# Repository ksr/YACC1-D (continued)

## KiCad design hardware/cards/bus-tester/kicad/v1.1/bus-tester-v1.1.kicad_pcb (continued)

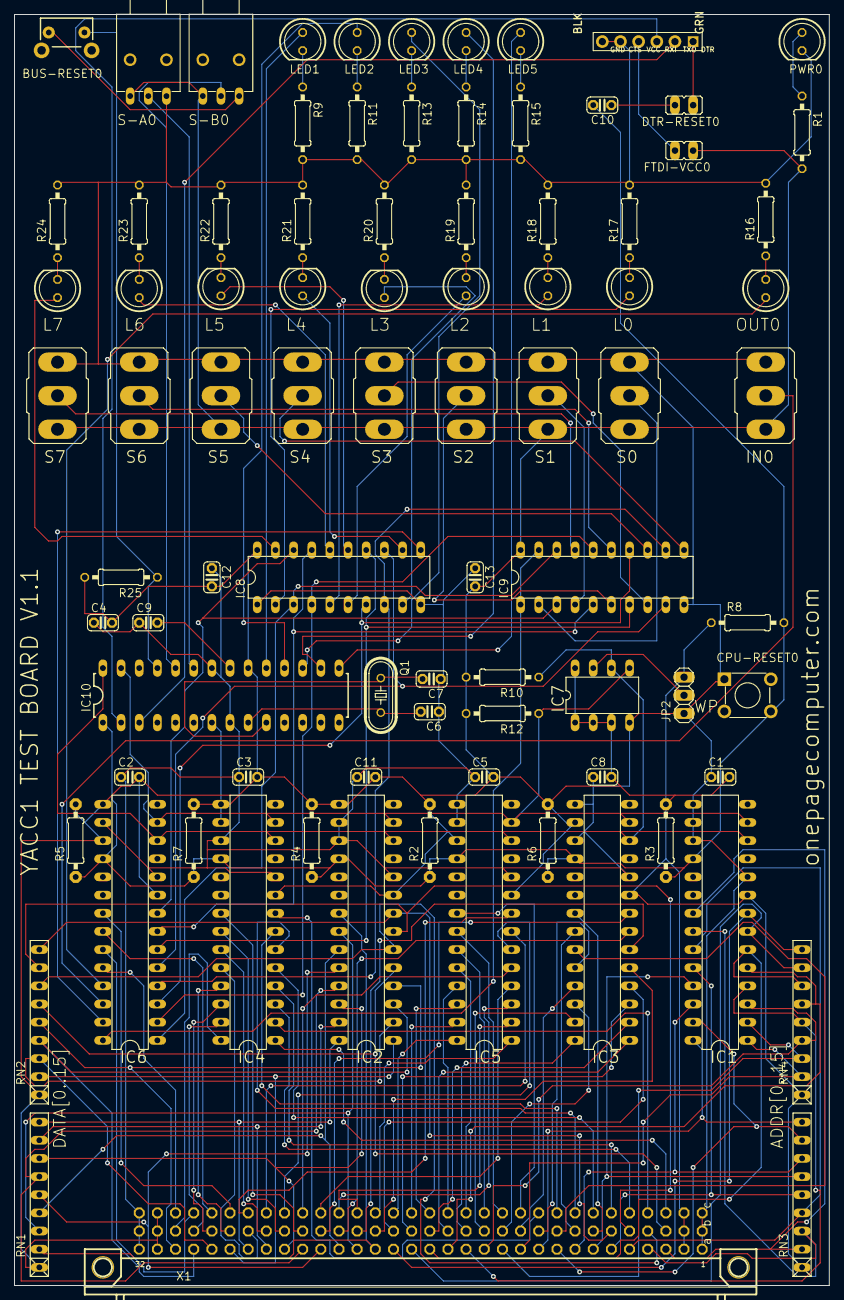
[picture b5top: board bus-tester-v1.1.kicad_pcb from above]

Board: 2 copper layers, 114.0 x 177.8 mm, 86 parts (0 on the bottom side), 149 nets.

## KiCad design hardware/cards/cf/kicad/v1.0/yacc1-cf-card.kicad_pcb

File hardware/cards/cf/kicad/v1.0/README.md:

# yacc1-cf-card v1.0 — KiCad design (generated from `cf_netlist.py`)

> **Not built (never ordered).** This design is the basis for the CF section planned on the memory card (decided
> 2026-09-24: same circuit, I/O-mapped on P8/P9, as the ROM and both emulators use; not designed yet). Theory:
> [`docs/cards/cf.md`](../../../../../docs/cards/cf.md).

The YACC1 CompactFlash card: a CF card in a commercial CF-to-IDE adapter, driven in 8-bit True IDE mode through two
I/O ports. P8 (write) is a 74LS175 latch holding the ATA register number (DA0-2) and a CF-reset bit; P9 (read/write)
is the selected ATA register through a 74LS245. A 74LS138 decodes the port and a 74LS32 gates the bus strobes. Theory of
operation: [`docs/cards/cf.md`](../../../../../docs/cards/cf.md).

**The circuit lives in `cf_netlist.py`** (parts, nets, no-connects, `check()`). `gen_cf.py` draws the schematic and
places the board from it; `build.sh` routes, checks and makes the fab files. To change the card, edit `cf_netlist.py`
and re-run `build.sh`. If you hand-edit the schematic or board in KiCad instead, stop running `gen_cf.py` (it rewrites
both) and say so here: from then on the KiCad files are the master and `compare_netlist.py` tells you whether they
still match `cf_netlist.py`.

`MASTER` marks this folder as hand-maintained (not written by `tools/eagle_to_kicad_all.py`).

## Files

| File | What it is |
|---|---|
| `cf_netlist.py` | **the circuit** (single source): 26 parts, 46 nets, 23 documented no-connect pins |
| `gen_cf.py` | writes the schematic, the placed board, the project and the local libraries (KiCad's Python) |
| `build.sh` | the whole pipeline, below; exit status 0 = every gate passed |
| `compare_netlist.py` | the netlist proof: schematic and board vs `cf_netlist.py`, pin for pin |
| `yacc1-cf-card.kicad_pro` | project: design rules (0.25 mm min track/clearance; net class Default 0.3 mm track / 0.25 mm clearance, via 0.8/0.4; class Power = VCC, GND, PIN20: 0.6 mm track / 0.3 mm clearance, via 1.0/0.5; 0.5 mm copper-to-edge) |
| `yacc1-cf-card.kicad_sch` | schematic, one A3 sheet in functional groups (bus connector, decode + strobe gating, P8 latch, data buffer, IDE header + pull-ups + adapter power, LEDs, power + decoupling, design notes); no text overlaps anything and nothing leaves the frame (`tools/kicad/sch_overlaps.py`: 0 / 0 / 0, frame 0) |
| `yacc1-cf-card.kicad_pcb` | the routed 2-layer board |
| `yacc1-cf-card.ses` | the Freerouting result imported into the board |
| `blank-card-v3.2-eagle.kicad_sym` | local symbol `FABC96R`: the bus connector as three 32-pin units (rows a/b/c), pin numbers A1..C32, pin names = the V3.2 bus signals (from the blank card's pads); 5.08 mm pins so the three-character pin numbers clear the body and the no-connect flags |
| `blank-card-v3.2-eagle.pretty/FABC96R.kicad_mod` | the bus connector footprint, copied unchanged from `hardware/bus/blank-card/kicad/v3.2/` |
| `sym-lib-table`, `fp-lib-table` | the two local libraries (`${KIPRJMOD}`, nothing outside this folder) |
| `yacc1-cf-card-schematic.pdf` | schematic plot |
| `yacc1-cf-card-placement.pdf` | parts placement (silk + fab + outline) |
| `yacc1-cf-card-render-top.png` | 3D render, top |
| `yacc1-cf-card-bom.csv` | bill of materials from the schematic (grouped by value + footprint) |
| `gerbers/`, `yacc1-cf-card-gerbers.zip` | F/B copper, mask, silk, Edge.Cuts, Excellon drill (mm) + drill map, job file |
| `reports/` | DRC and ERC (`.rpt` + `.json`), the schematic netlist (`.net`), `netlist-proof.txt`, Freerouting logs |

## Rebuild

    hardware/cards/cf/kicad/v1.0/build.sh            # ~1 minute; NOROUTE=1 skips routing and fab files

1. `gen_cf.py`: local libraries; the schematic (KiCad standard symbols from `74xx`, `Device`, `Connector_Generic`,
   `power`, embedded in `lib_symbols`; every pin gets a short wire stub to a net label or a power symbol, no-connect
   flags on the `NO_CONNECT` pins and the 69 bus pins the card does not use; Reference/Value go where the library puts
   them unless that is on the body (the 74xx gates) or drawn rotated (R, C, LED): then above/below the body, or beside
   it for parts with pins only top and bottom (`auto_fields()`); KiCad re-saves it with
   `kicad-cli sch upgrade`); the board, started from a copy of the blank V3.2 card (outline, X1 at its place, the
   site text; its own power LED and 330R removed because their footprints and values differ from the netlist's
   LED1/R7), every footprint from `PARTS`, every pad on its net, GND pours on both layers, 4 mm copper keepouts
   round the two DIN mounting screws; each footprint linked to its symbol (DRC schematic parity is clean).
2. Specctra DSN without the pours (`tools/kicad/kicad_route.py export_dsn`), so GND is routed as tracks.
3. Freerouting 1.9 (`-mt 1`, 20-minute watchdog). About 30-40 s here (auto-route ~4 s, then the optimizer).
4. Import, straight-stitch any trivial 2-pad net the router missed, pull edge-hugging tracks in, fill the pours,
   and give any GND pad whose thermal spokes land on a local fill island a solid pad-level connection (such a pad
   is already track-routed; the build log names them, typically 3-7 IC/cap GND pins; the set varies run to run).
5. DRC with schematic parity. 6. ERC. 7. Netlist proof. 8. Gerbers, drill, zip, placement PDF, render, BOM,
   schematic PDF.

Freerouting is not fully deterministic: each rebuild gives a slightly different (equally valid) routing.

## Results (build of 2026-09-23)

- **Netlist proof: MATCH.** The netlist KiCad exports from the schematic and the pad nets of the board each equal
  `cf_netlist.py` exactly: 46 nets, 171 net pins, same names; the 92 unconnected pins are exactly the 23 `NO_CONNECT`
  pins plus the 69 unused bus pins; all 26 parts with their values and footprints (`reports/netlist-proof.txt`).
- **DRC: 0 errors, 0 unconnected, schematic parity 0.** 8 cosmetic warnings, all inherited from the blank card's
  connector footprint: 4 `silk_edge_clearance` (X1's outline silk reaches the board edge) and 2 + 2 `text_height` /
  `text_thickness` (X1's 0.73 mm "1"/"32" row markers).
- **ERC: 0 errors, 1 warning:** `isolated_pin_label` on `SRST`, U3 Q3 (latch bit 3, true output), which is a
  one-pin net by design (a probe point; the card uses -Q3 = `-SRST`).
- Board **177.83 x 114.02 mm** (the blank V3.2 card outline), **2 layers**, through-hole only; 26 parts (5 ICs,
  X1, J1, J2, JP1, RN1, R1-R7, LED1-3, C1-C6); ~500 track segments, ~20 vias; signals 0.3 mm, VCC/GND/PIN20 0.6 mm,
  GND pour both sides.

## Notes on names

- `PARTS` names `Device:CP` for C6; KiCad 10 calls that symbol `Device:C_Polarized` (same pins, 1 = +), which the
  schematic uses.
- Schematic label nets are named `/NAME` by KiCad (sheet prefix); the board uses the same names so "Update PCB from
  Schematic" is a no-op. `compare_netlist.py` strips the `/`.

## Before ordering (for a human)

1. **Check the CF-to-IDE adapter against J1**: which way the adapter plugs on (pin 1 is the square pad, top left,
   marked "1" on the silk; the shroud key faces the ICs), how far its body overhangs the board and whether it clears
   R1-R4, RN1, JP1 and the LEDs, and whether it needs the card-edge side free.
2. **Check the adapter's power input**: J2 is a plain 1x4 0.1" header, pin 1 = +5 V, 2 and 3 = GND, 4 = not
   connected; confirm the cable/connector the adapter in hand takes (floppy Berg vs. 0.1") and the pin order. Fit JP1 only
   if the adapter takes +5 V on IDE pin 20 (many do not, and pin 20 is the key position on keyed cables).
3. LED colours and the 1k series resistors (~2.5 mA) to taste.
4. Optional hand tidying: placement is functional, not beautiful (IC row at the connector, pull-ups beside J1, LEDs
   bottom right); the router's track layout can be cleaned up in pcbnew. Re-run DRC and `compare_netlist.py` after
   any hand edit, and stop using `gen_cf.py` once you do.
5. Check the X1 footprint's position against a real blank V3.2 card / backplane (it is copied from the blank card
   conversion, which was not fabricated).

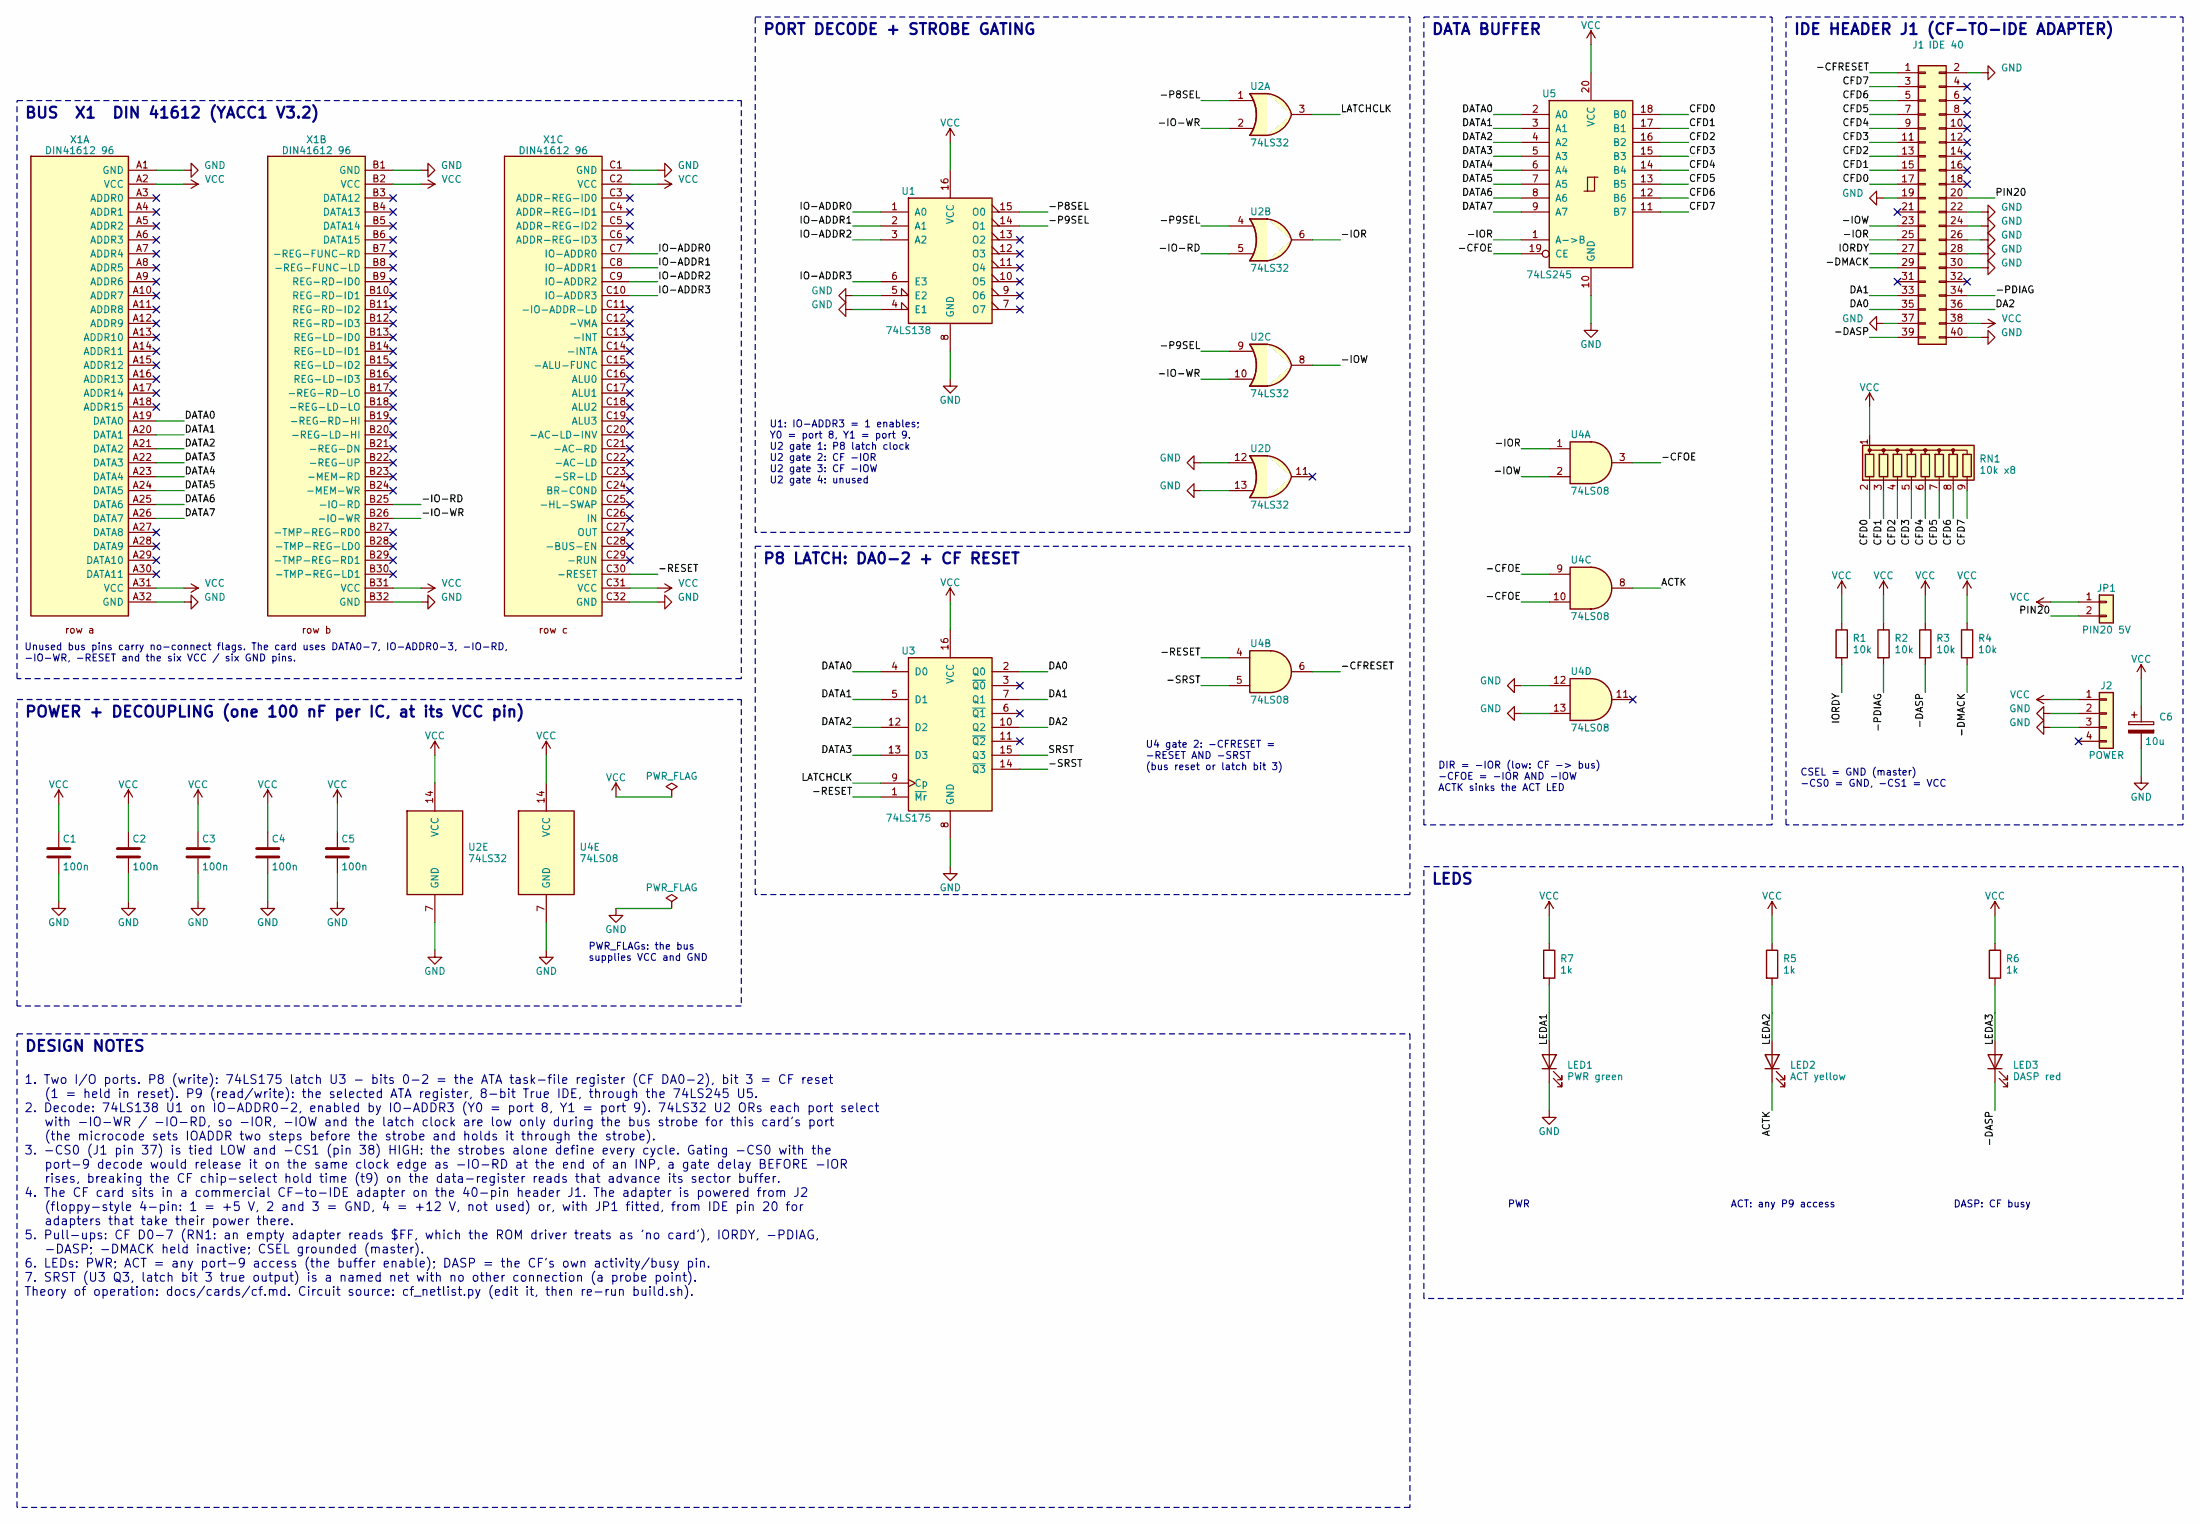
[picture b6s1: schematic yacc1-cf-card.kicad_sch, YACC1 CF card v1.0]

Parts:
C1, C2, C3, C4, C5: 100n; C_Disc_D5.0mm_W2.5mm_P5.00mm
C6: 10u; CP_Radial_D5.0mm_P2.00mm
J1: IDE 40; IDC-Header_2x20_P2.54mm_Vertical
J2: POWER; PinHeader_1x04_P2.54mm_Vertical
JP1: PIN20 5V; PinHeader_1x02_P2.54mm_Vertical
LED1: PWR green; LED_D5.0mm
LED2: ACT yellow; LED_D5.0mm
LED3: DASP red; LED_D5.0mm
R1, R2, R3, R4: 10k; R_Axial_DIN0207_L6.3mm_D2.5mm_P10.16mm_Horizontal
R5, R6, R7: 1k; R_Axial_DIN0207_L6.3mm_D2.5mm_P10.16mm_Horizontal
RN1: 10k x8; R_Array_SIP9
U1: 74LS138; DIP-16_W7.62mm
U2: 74LS32; DIP-14_W7.62mm
U3: 74LS175; DIP-16_W7.62mm
U4: 74LS08; DIP-14_W7.62mm
U5: 74LS245; DIP-20_W7.62mm
X1: DIN41612 96; FABC96R

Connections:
/-CFOE: U4.3, U4.9, U4.10, U5.19 (CE)
/-CFRESET: J1.1, U4.6
/-DASP: J1.39, LED3.1 (K), R3.2
/-DMACK: J1.29, R4.2
/-IO-RD: U2.5, X1.B25 (-IO-RD)
/-IO-WR: U2.2, U2.10, X1.B26 (-IO-WR)
/-IOR: J1.25, U2.6, U4.1, U5.1 (A->B)
/-IOW: J1.23, U2.8, U4.2
/-P8SEL: U1.15 (O0), U2.1
/-P9SEL: U1.14 (O1), U2.4, U2.9
/-PDIAG: J1.34, R2.2
/-RESET: U3.1 (~Mr), U4.4, X1.C30 (-RESET)
/-SRST: U3.14 (~Q3), U4.5
/ACTK: LED2.1 (K), U4.8
/CFD0: J1.17, RN1.2 (R1), U5.18 (B0)
/CFD1: J1.15, RN1.3 (R2), U5.17 (B1)
/CFD2: J1.13, RN1.4 (R3), U5.16 (B2)
/CFD3: J1.11, RN1.5 (R4), U5.15 (B3)
/CFD4: J1.9, RN1.6 (R5), U5.14 (B4)
/CFD5: J1.7, RN1.7 (R6), U5.13 (B5)
/CFD6: J1.5, RN1.8 (R7), U5.12 (B6)
/CFD7: J1.3, RN1.9 (R8), U5.11 (B7)
/DA0: J1.35, U3.2 (Q0)
/DA1: J1.33, U3.7 (Q1)
/DA2: J1.36, U3.10 (Q2)
/DATA0: U3.4 (D0), U5.2 (A0), X1.A19 (DATA0)
/DATA1: U3.5 (D1), U5.3 (A1), X1.A20 (DATA1)
/DATA2: U3.12 (D2), U5.4 (A2), X1.A21 (DATA2)
/DATA3: U3.13 (D3), U5.5 (A3), X1.A22 (DATA3)
/DATA4: U5.6 (A4), X1.A23 (DATA4)
/DATA5: U5.7 (A5), X1.A24 (DATA5)
/DATA6: U5.8 (A6), X1.A25 (DATA6)
/DATA7: U5.9 (A7), X1.A26 (DATA7)
/IO-ADDR0: U1.1 (A0), X1.C7 (IO-ADDR0)
/IO-ADDR1: U1.2 (A1), X1.C8 (IO-ADDR1)
/IO-ADDR2: U1.3 (A2), X1.C9 (IO-ADDR2)
/IO-ADDR3: U1.6 (E3), X1.C10 (IO-ADDR3)
/IORDY: J1.27, R1.2
/LATCHCLK: U2.3, U3.9 (Cp)
/LEDA1: LED1.2 (A), R7.2
/LEDA2: LED2.2 (A), R5.2
/LEDA3: LED3.2 (A), R6.2
/PIN20: J1.20, JP1.2
/SRST: U3.15 (Q3)
GND: C1.2, C2.2, C3.2, C4.2, C5.2, C6.2, J1.2, J1.19, J1.22, J1.24, J1.26, J1.28, J1.30, J1.37, J1.40, J2.2, J2.3, LED1.1 (K), U1.4 (E1), U1.5 (E2), U1.8 (GND), U2.7 (GND), U2.12, U2.13, U3.8 (GND), U4.7 (GND), U4.12, U4.13, U5.10 (GND), X1.A1 (GND), X1.A32 (GND), X1.B1 (GND), X1.B32 (GND), X1.C1 (GND), X1.C32 (GND)
VCC: C1.1, C2.1, C3.1, C4.1, C5.1, C6.1, J1.38, J2.1, JP1.1, R1.1, R2.1, R3.1, R4.1, R5.1, R6.1, R7.1, RN1.1 (common), U1.16 (VCC), U2.14 (VCC), U3.16 (VCC), U4.14 (VCC), U5.20 (VCC), X1.A2 (VCC), X1.A31 (VCC), X1.B2 (VCC), X1.B31 (VCC), X1.C2 (VCC), X1.C31 (VCC)

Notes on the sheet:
DIR = -IOR (low: CF -> bus) -CFOE = -IOR AND -IOW ACTK sinks the ACT LED
U4 gate 2: -CFRESET = -RESET AND -SRST (bus reset or latch bit 3)
1. Two I/O ports. P8 (write): 74LS175 latch U3 - bits 0-2 = the ATA task-file register (CF DA0-2), bit 3 = CF reset (1 = held in reset). P9 (read/write): the selected ATA register, 8-bit True IDE, through the 74LS245 U5. 2. Decode: 74LS138 U1 on IO-ADDR0-2, enabled by IO-ADDR3 (Y0 = port 8, Y1 = po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
Unused bus pins carry no-connect flags. The card uses DATA0-7, IO-ADDR0-3, -IO-RD, -IO-WR, -RESET and the six VCC / six GND pins.
DATA BUFFER
CSEL = GND (master) -CS0 = GND, -CS1 = VCC
POWER + DECOUPLING (one 100 nF per IC, at its VCC pin)
ACT: any P9 access
DASP: CF busy
IDE HEADER J1 (CF-TO-IDE ADAPTER)
PWR
PWR_FLAGs: the bus supplies VCC and GND
PORT DECODE + STROBE GATING
DESIGN NOTES
U1: IO-ADDR3 = 1 enables; Y0 = port 8, Y1 = port 9. U2 gate 1: P8 latch clock U2 gate 2: CF -IOR U2 gate 3: CF -IOW U2 gate 4: unused
BUS X1 DIN 41612 (YACC1 V3.2)
P8 LATCH: DA0-2 + CF RESET
LEDS

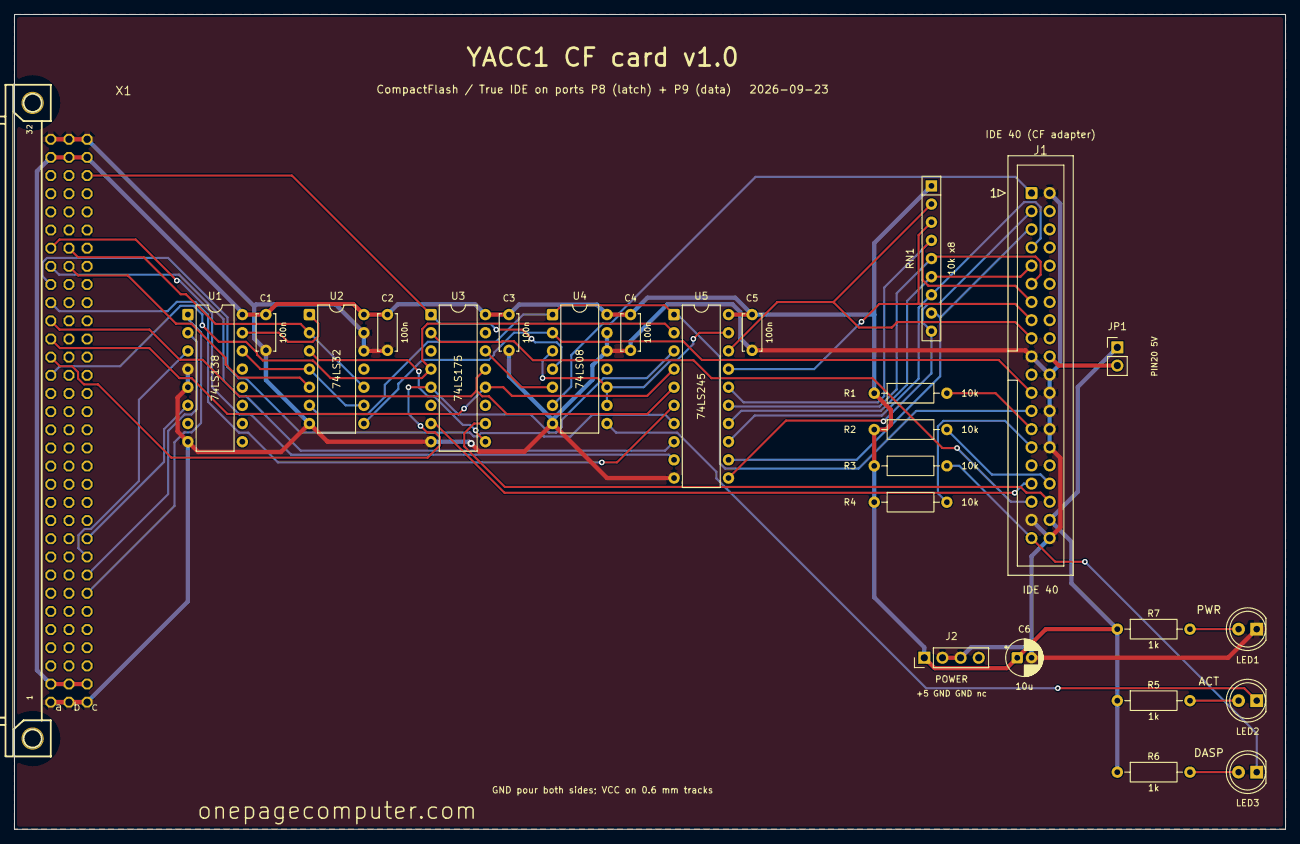
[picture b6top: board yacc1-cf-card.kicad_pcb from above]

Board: 2 copper layers, 177.8 x 114.0 mm, 26 parts (0 on the bottom side), 45 nets.

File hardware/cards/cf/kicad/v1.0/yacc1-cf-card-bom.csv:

"Refs","Value","Footprint","Qty"
"C1-C5","100n","Capacitor_THT:C_Disc_D5.0mm_W2.5mm_P5.00mm","5"
"C6","10u","Capacitor_THT:CP_Radial_D5.0mm_P2.00mm","1"
"J1","IDE 40","Connector_IDC:IDC-Header_2x20_P2.54mm_Vertical","1"
"J2","POWER","Connector_PinHeader_2.54mm:PinHeader_1x04_P2.54mm_Vertical","1"
"JP1","PIN20 5V","Connector_PinHeader_2.54mm:PinHeader_1x02_P2.54mm_Vertical","1"
"LED1","PWR green","LED_THT:LED_D5.0mm","1"
"LED2","ACT yellow","LED_THT:LED_D5.0mm","1"
"LED3","DASP red","LED_THT:LED_D5.0mm","1"
"R1-R4","10k","Resistor_THT:R_Axial_DIN0207_L6.3mm_D2.5mm_P10.16mm_Horizontal","4"
"R5-R7","1k","Resistor_THT:R_Axial_DIN0207_L6.3mm_D2.5mm_P10.16mm_Horizontal","3"
"RN1","10k x8","Resistor_THT:R_Array_SIP9","1"
"U1","74LS138","Package_DIP:DIP-16_W7.62mm","1"
"U2","74LS32","Package_DIP:DIP-14_W7.62mm","1"
"U3","74LS175","Package_DIP:DIP-16_W7.62mm","1"
"U4","74LS08","Package_DIP:DIP-14_W7.62mm","1"
"U5","74LS245","Package_DIP:DIP-20_W7.62mm","1"
"X1","DIN41612 96","blank-card-v3.2-eagle:FABC96R","1"

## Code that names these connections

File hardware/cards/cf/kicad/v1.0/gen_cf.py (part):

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                elif g[0] == "circle":
                    c, r = sfind(g, "center")[0], float(sfind(g, "radius")[0][1])
                    self.body[unit] += [(float(c[1]) - r, float(c[2]) - r), (float(c[1]) + r, float(c[2]) + r)]
            for p in sfind(sub, "pin"):
                at = sfind(p, "at")[0]
                self.pins[unit].append(dict(num=unq(sfind(p, "number")[0][1]), x=float(at[1]), y=float(at[2]),
                                            ang=int(float(at[3])), etype=p[1]))
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    S.box(gx(5), gx(11), gx(57), gx(52.5), "BUS  X1  DIN 41612 (YACC1 V3.2)")
    for i, u in enumerate((1, 2, 3)):
        S.part("X1", u, gx(6 + 17 * i), gx(16), fields={"Reference": (8.89, -5.6), "Value": (8.89, -3.6)})
    S.text(gx(5.5), gx(50), "Unused bus pins carry no-connect flags. The card uses DATA0-7, IO-ADDR0-3, -IO-RD,\n"
           "-IO-WR, -RESET and the six VCC / six GND pins.", size=1.27)

    # --- decode + strobe gating ------------------------------------------------------------------------------------
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        place(c, x + 7.62 + 3.3, TOP, 270)        # the 100 nF: pad 1 (VCC) level with the VCC pin, pad 2 below it
    J1X, J1Y = 160.0, 35.0
    place("J1", J1X, J1Y)                         # pin 1 top left; odd pins left column, even right
    place("RN1", 146.0, 34.0, 270)                # common pin 1 at the top, CFD0..7 downwards beside J1's data pins
    for i, r in enumerate(("R1", "R2", "R3", "R4")):
        place(r, 138.0, 63.0 + 5.08 * i)          # the status pull-ups: VCC end left, J1 end right
    place("JP1", 172.0, J1Y + 9 * 2.54 - 1.27)    # beside J1 pin 20
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    pro["net_settings"]["classes"] = [d, pw]
    pro["net_settings"]["netclass_patterns"] = [{"netclass": "Power", "pattern": "VCC"},
                                                {"netclass": "Power", "pattern": "GND"},
                                                {"netclass": "Power", "pattern": "/PIN20"}]
    pro["meta"]["filename"] = PROJ + ".kicad_pro"
    pro["sheets"] = [[root_uuid, "Root"]]
    json.dump(pro, open(os.path.join(HERE, PROJ + ".kicad_pro"), "w"), indent=2)
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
